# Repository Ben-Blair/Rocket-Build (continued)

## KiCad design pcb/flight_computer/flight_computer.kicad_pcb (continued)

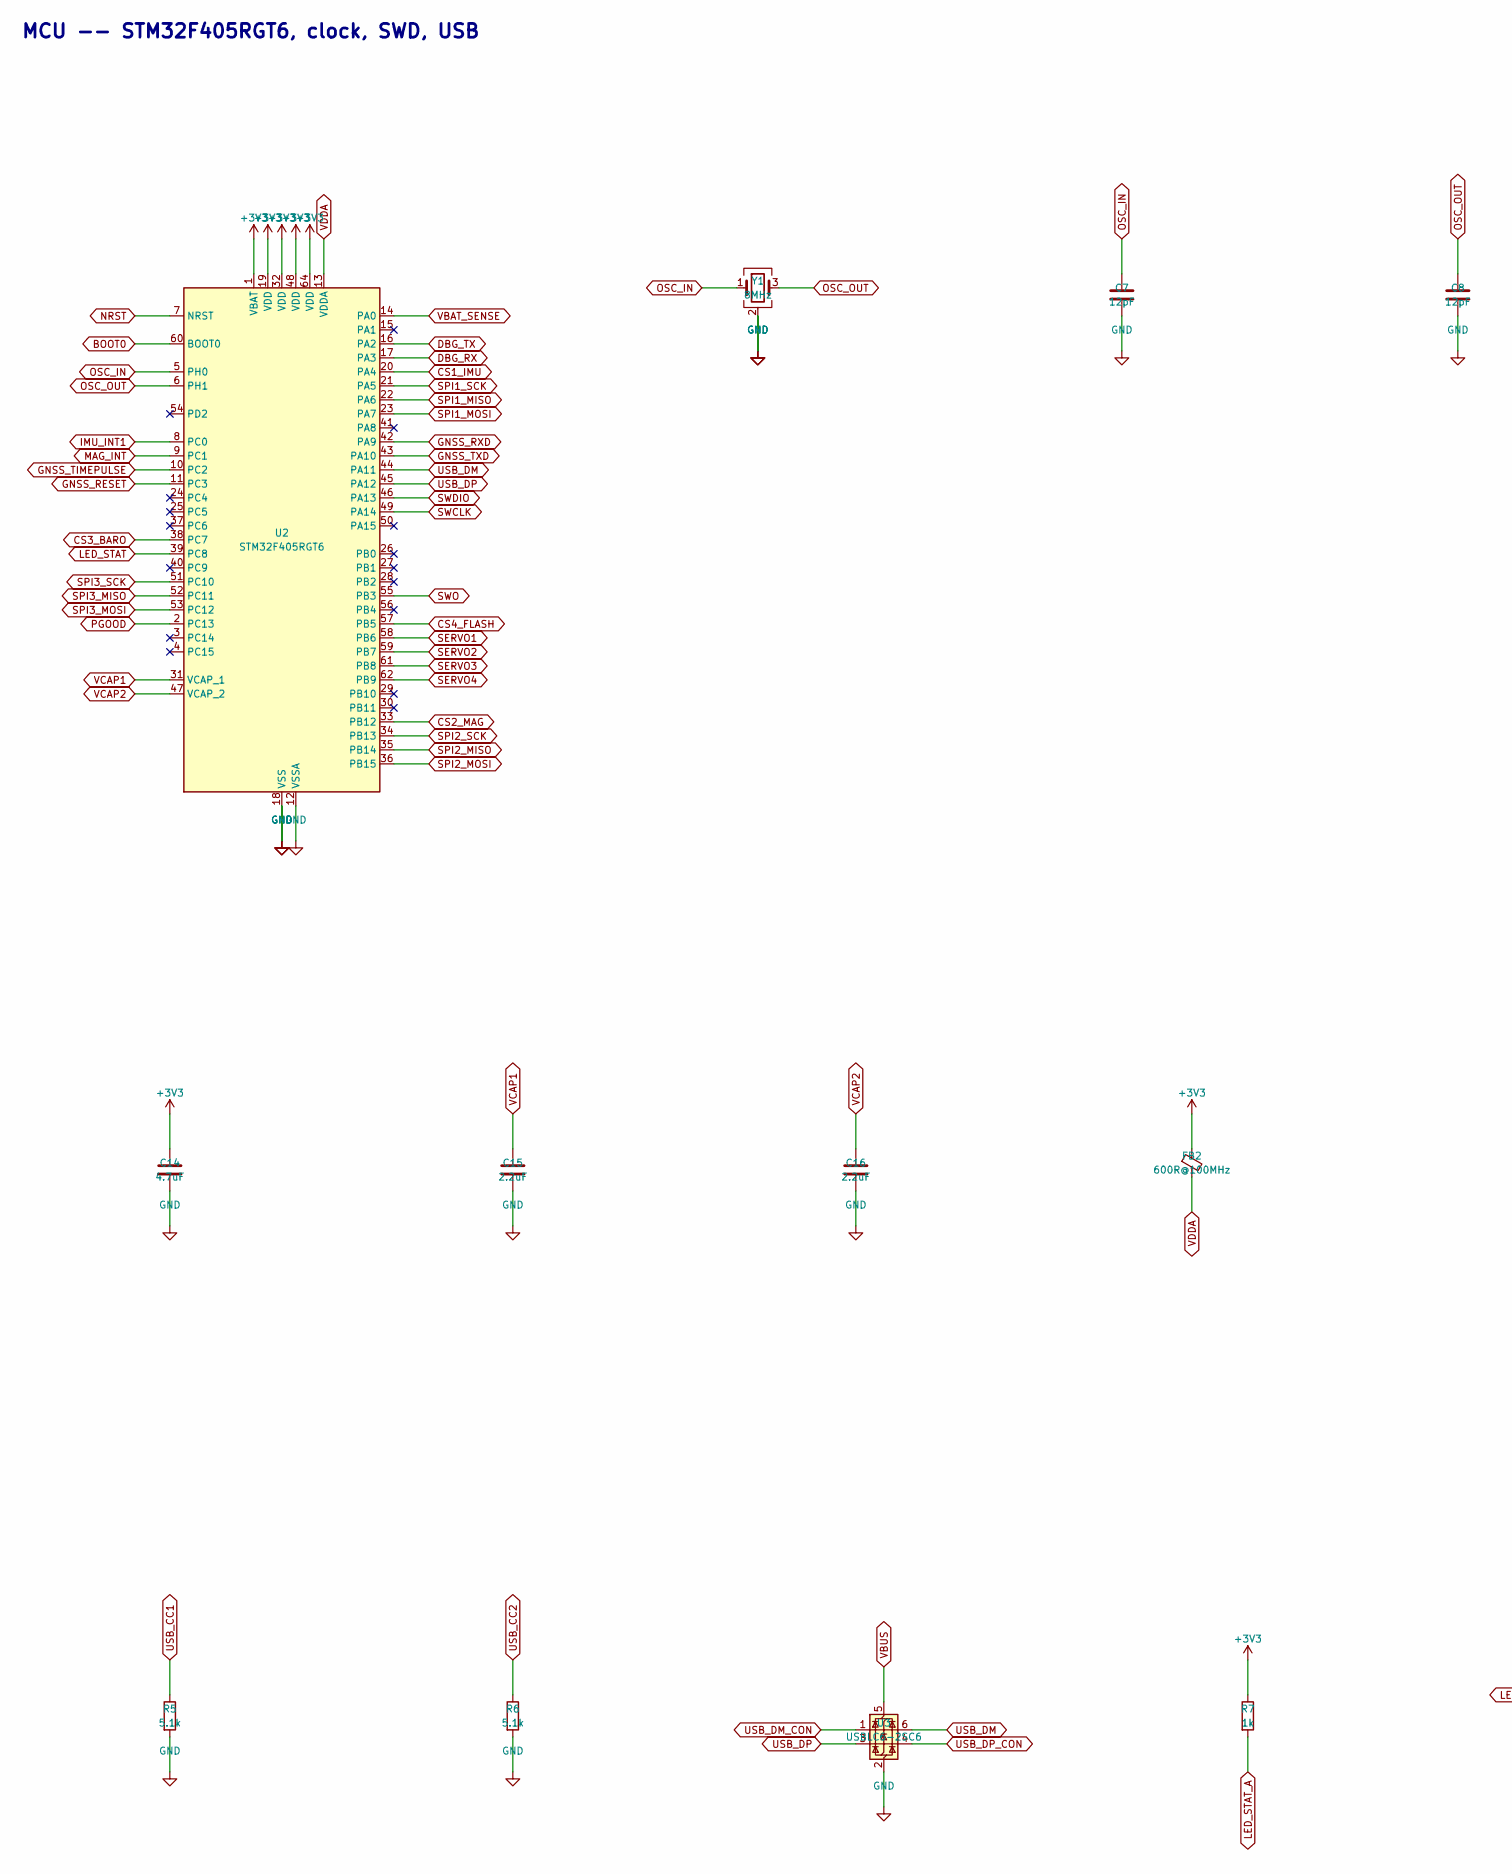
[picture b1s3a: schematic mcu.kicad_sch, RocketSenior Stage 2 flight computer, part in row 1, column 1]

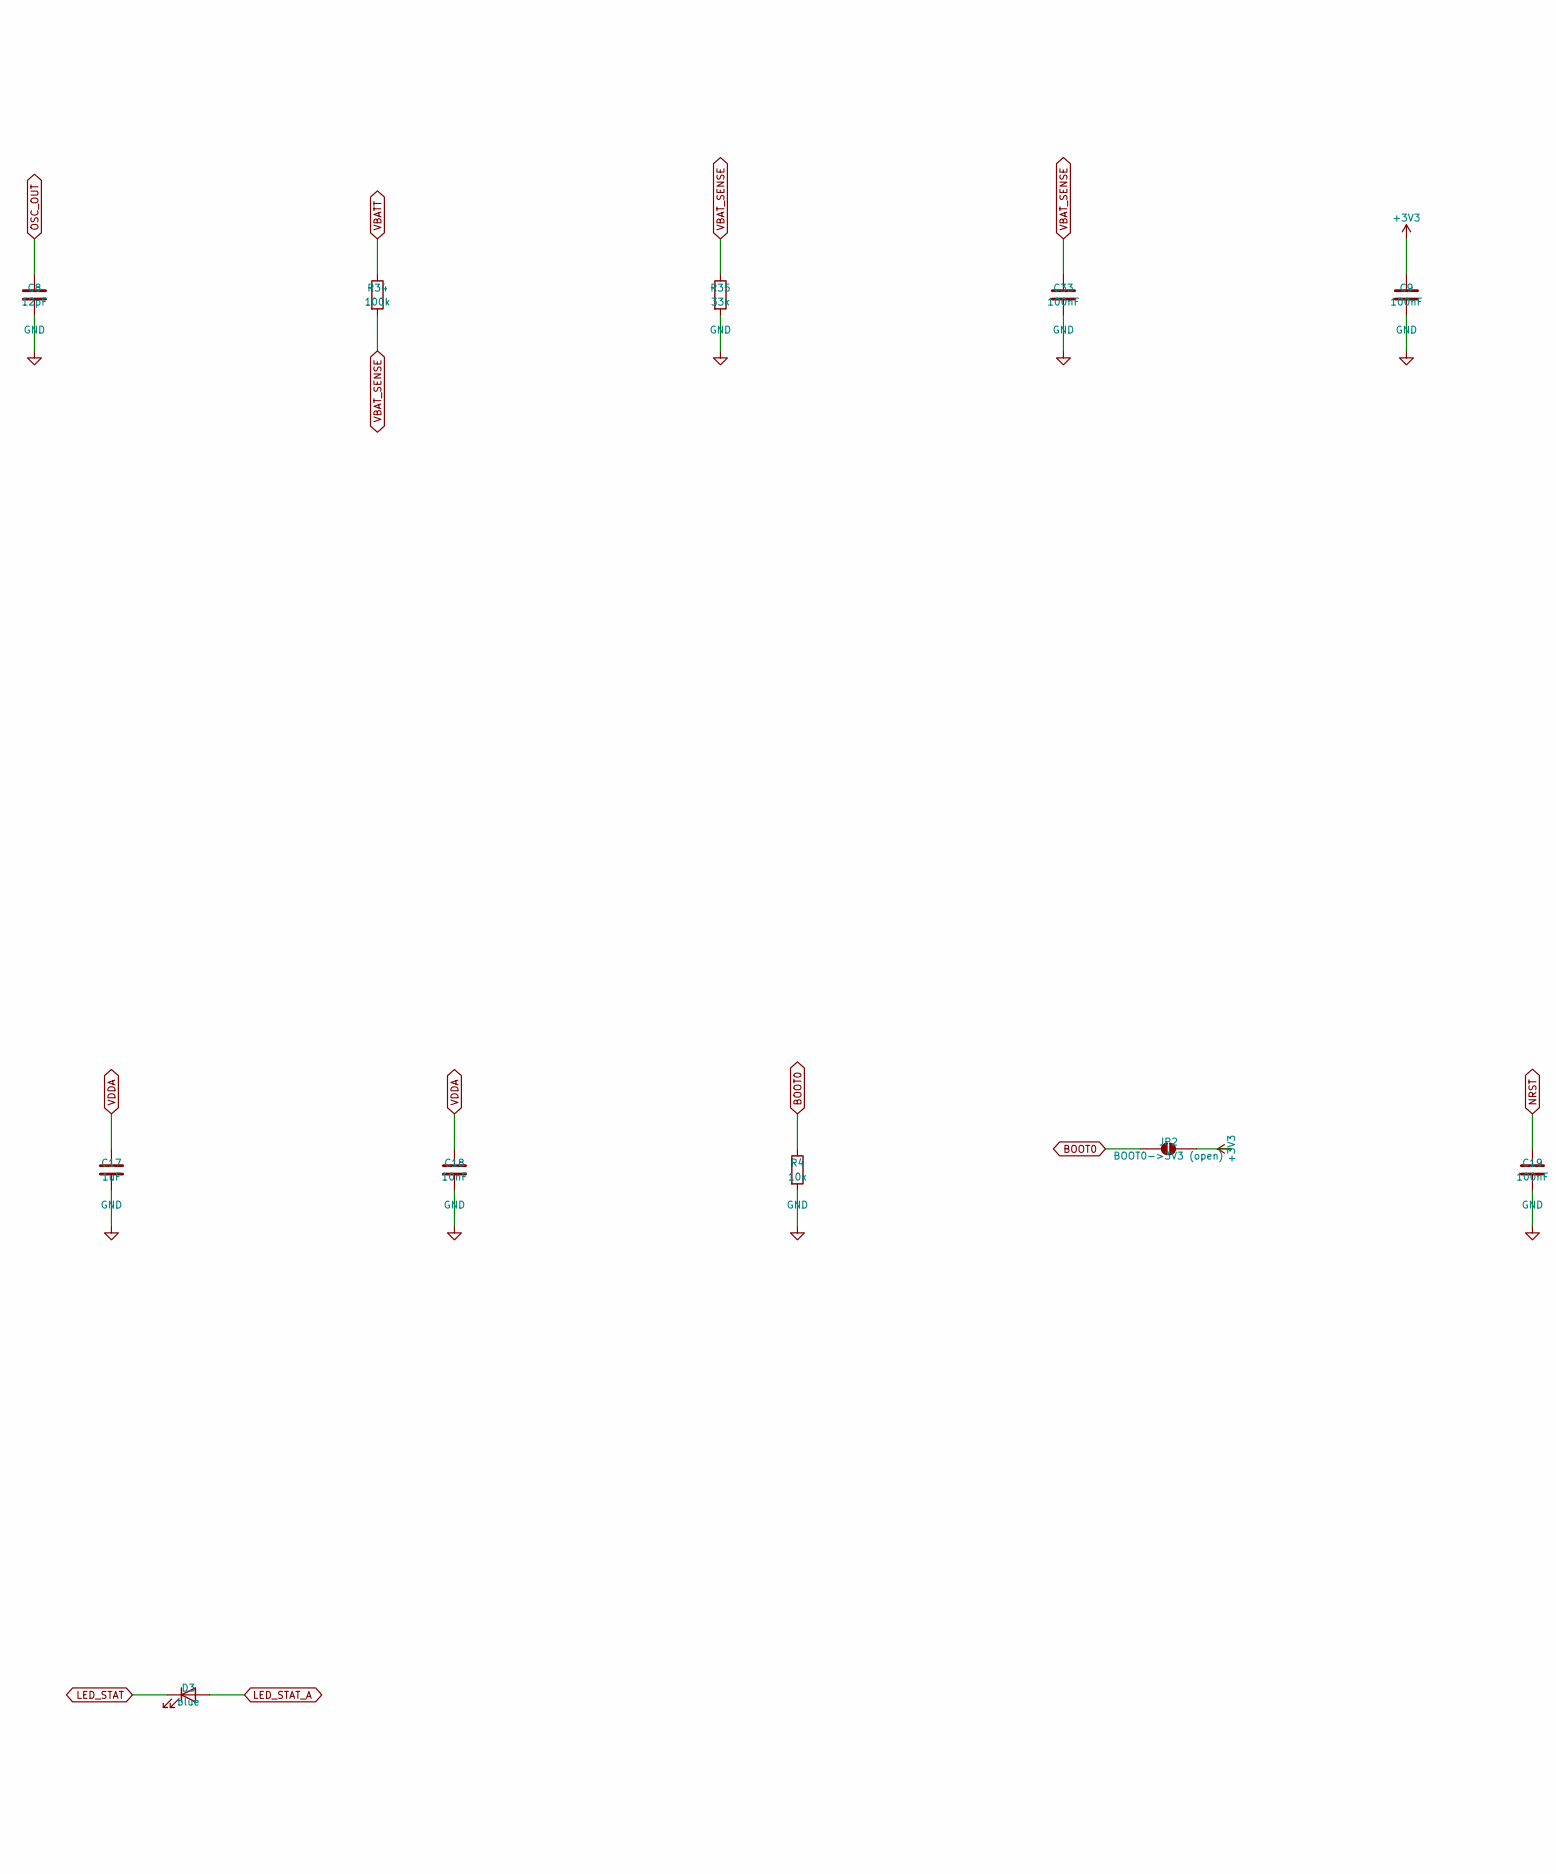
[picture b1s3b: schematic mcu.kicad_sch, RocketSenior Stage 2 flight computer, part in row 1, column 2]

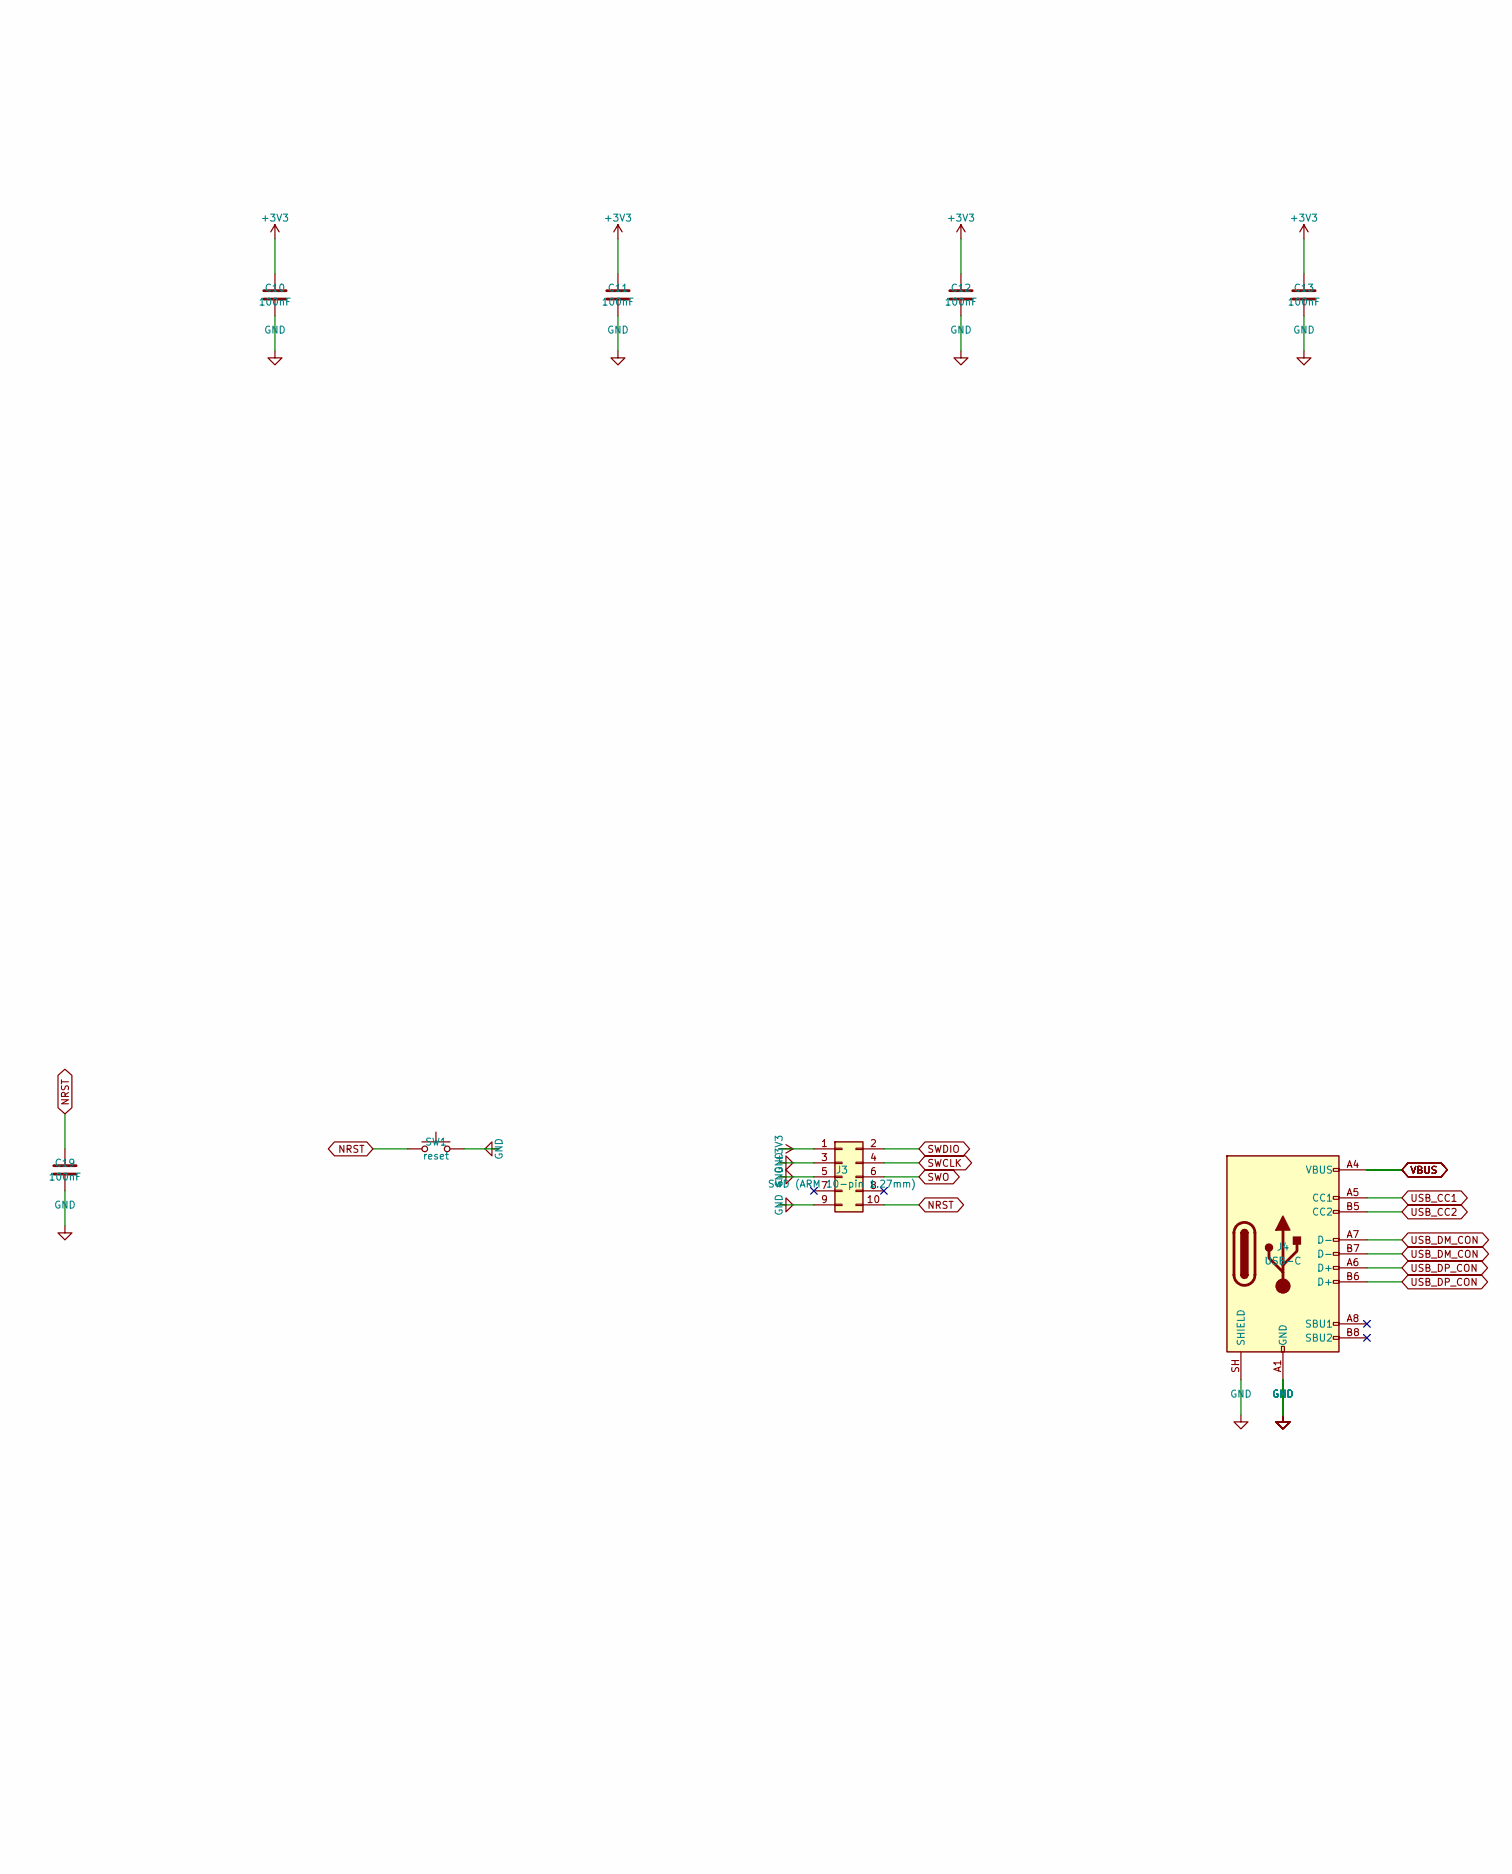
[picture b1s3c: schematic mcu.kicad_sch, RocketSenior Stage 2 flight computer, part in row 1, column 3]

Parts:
C7, C8: 12pF; C_0402_1005Metric
C9, C10, C11, C12, C13, C19, C33: 100nF; C_0402_1005Metric
C14: 4.7uF; C_0805_2012Metric
C15, C16: 2.2uF; C_0805_2012Metric
C17: 1uF; C_0603_1608Metric
C18: 10nF; C_0402_1005Metric
D3: blue; LED_0603_1608Metric
FB2: 600R@100MHz; L_0603_1608Metric
J3: SWD (ARM 10-pin 1.27mm); PinHeader_2x05_P1.27mm_Vertical_SMD
J4: USB-C; USB_C_Receptacle_HRO_TYPE-C-31-M-12
JP2: BOOT0->3V3 (open); SolderJumper-2_P1.3mm_Open_Pad1.0x1.5mm
R4: 10k; R_0402_1005Metric
R5, R6: 5.1k; R_0402_1005Metric
R7: 1k; R_0402_1005Metric
R34: 100k; R_0402_1005Metric
R35: 33k; R_0402_1005Metric
SW1: reset; SW_SPST_TL3342
U2: STM32F405RGT6; LQFP-64_10x10mm_P0.5mm
U3: USBLC6-2SC6; SOT-23-6
Y1: 8MHz; Crystal_SMD_3225-4Pin_3.2x2.5mm

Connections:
+3V3: C9.1, C10.1, C11.1, C12.1, C13.1, C14.1, FB2.1, J3.1, JP2.2 (B), R7.1, U2.1 (VBAT), U2.19 (VDD), U2.32 (VDD), U2.48 (VDD), U2.64 (VDD); also elsewhere on the board
BOOT0: JP2.1 (A), R4.1, U2.60 (BOOT0)
CS1_IMU: U2.20 (PA4); also elsewhere on the board
CS2_MAG: U2.33 (PB12); also elsewhere on the board
CS3_BARO: U2.38 (PC7); also elsewhere on the board
CS4_FLASH: U2.57 (PB5); also elsewhere on the board
DBG_RX: U2.17 (PA3); also elsewhere on the board
DBG_TX: U2.16 (PA2); also elsewhere on the board
GND: C7.2, C8.2, C9.2, C10.2, C11.2, C12.2, C13.2, C14.2, C15.2, C16.2, C17.2, C18.2, C19.2, C33.2, J3.3, J3.5, J3.9, J4.A1 (GND), J4.A12 (GND), J4.B1 (GND), J4.B12 (GND), J4.SH (SHIELD), R4.2, R5.2, R6.2, R35.2, SW1.2, U2.12 (VSSA), U2.18 (VSS), U2.63 (VSS), U3.2 (GND), Y1.2 (G), Y1.4 (G); also elsewhere on the board
GNSS_RESET: U2.11 (PC3); also elsewhere on the board
GNSS_RXD: U2.42 (PA9); also elsewhere on the board
GNSS_TIMEPULSE: U2.10 (PC2); also elsewhere on the board
GNSS_TXD: U2.43 (PA10); also elsewhere on the board
IMU_INT1: U2.8 (PC0); also elsewhere on the board
LED_STAT: D3.1 (K), U2.39 (PC8)
LED_STAT_A: D3.2 (A), R7.2
MAG_INT: U2.9 (PC1); also elsewhere on the board
NRST: C19.1, J3.10, SW1.1, U2.7 (NRST)
OSC_IN: C7.1, U2.5 (PH0), Y1.1
OSC_OUT: C8.1, U2.6 (PH1), Y1.3
PGOOD: U2.2 (PC13); also elsewhere on the board
SERVO1: U2.58 (PB6); also elsewhere on the board
SERVO2: U2.59 (PB7); also elsewhere on the board
SERVO3: U2.61 (PB8); also elsewhere on the board
SERVO4: U2.62 (PB9); also elsewhere on the board
SPI1_MISO: U2.22 (PA6); also elsewhere on the board
SPI1_MOSI: U2.23 (PA7); also elsewhere on the board
SPI1_SCK: U2.21 (PA5); also elsewhere on the board
SPI2_MISO: U2.35 (PB14); also elsewhere on the board
SPI2_MOSI: U2.36 (PB15); also elsewhere on the board
SPI2_SCK: U2.34 (PB13); also elsewhere on the board
SPI3_MISO: U2.52 (PC11); also elsewhere on the board
SPI3_MOSI: U2.53 (PC12); also elsewhere on the board
SPI3_SCK: U2.51 (PC10); also elsewhere on the board
SWCLK: J3.4, U2.49 (PA14)
SWDIO: J3.2, U2.46 (PA13)
SWO: J3.6, U2.55 (PB3)
USB_CC1: J4.A5 (CC1), R5.1
USB_CC2: J4.B5 (CC2), R6.1
USB_DM: U2.44 (PA11), U3.6 (I/O1)
USB_DM_CON: J4.A7 (D-), J4.B7 (D-), U3.1 (I/O1)
USB_DP: U2.45 (PA12), U3.3 (I/O2)
USB_DP_CON: J4.A6 (D+), J4.B6 (D+), U3.4 (I/O2)
VBATT: R34.1; also elsewhere on the board
VBAT_SENSE: C33.1, R34.2, R35.1, U2.14 (PA0)
VBUS: J4.A4 (VBUS), J4.A9 (VBUS), J4.B4 (VBUS), J4.B9 (VBUS), U3.5 (VBUS); also elsewhere on the board
VCAP1: C15.1, U2.31 (VCAP_1)
VCAP2: C16.1, U2.47 (VCAP_2)
VDDA: C17.1, C18.1, FB2.2, U2.13 (VDDA)

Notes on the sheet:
MCU -- STM32F405RGT6, clock, SWD, USB

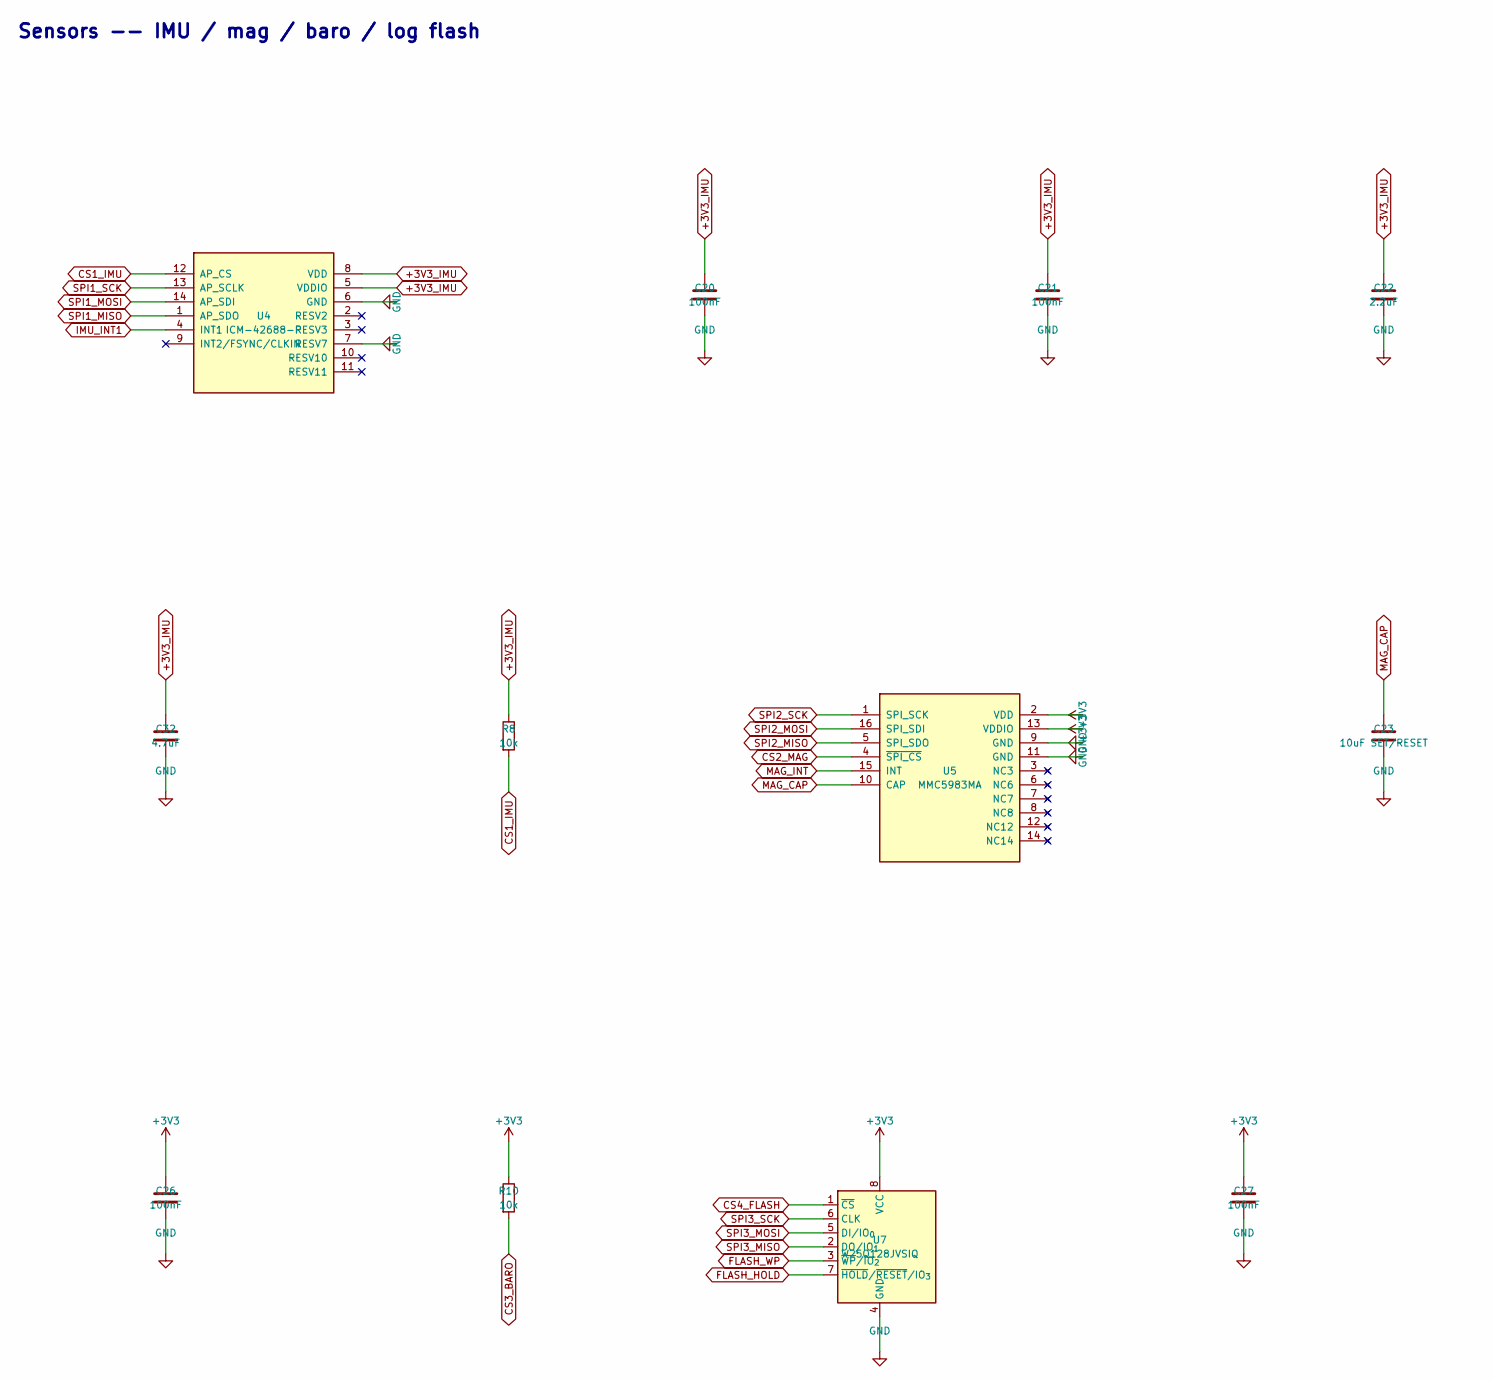
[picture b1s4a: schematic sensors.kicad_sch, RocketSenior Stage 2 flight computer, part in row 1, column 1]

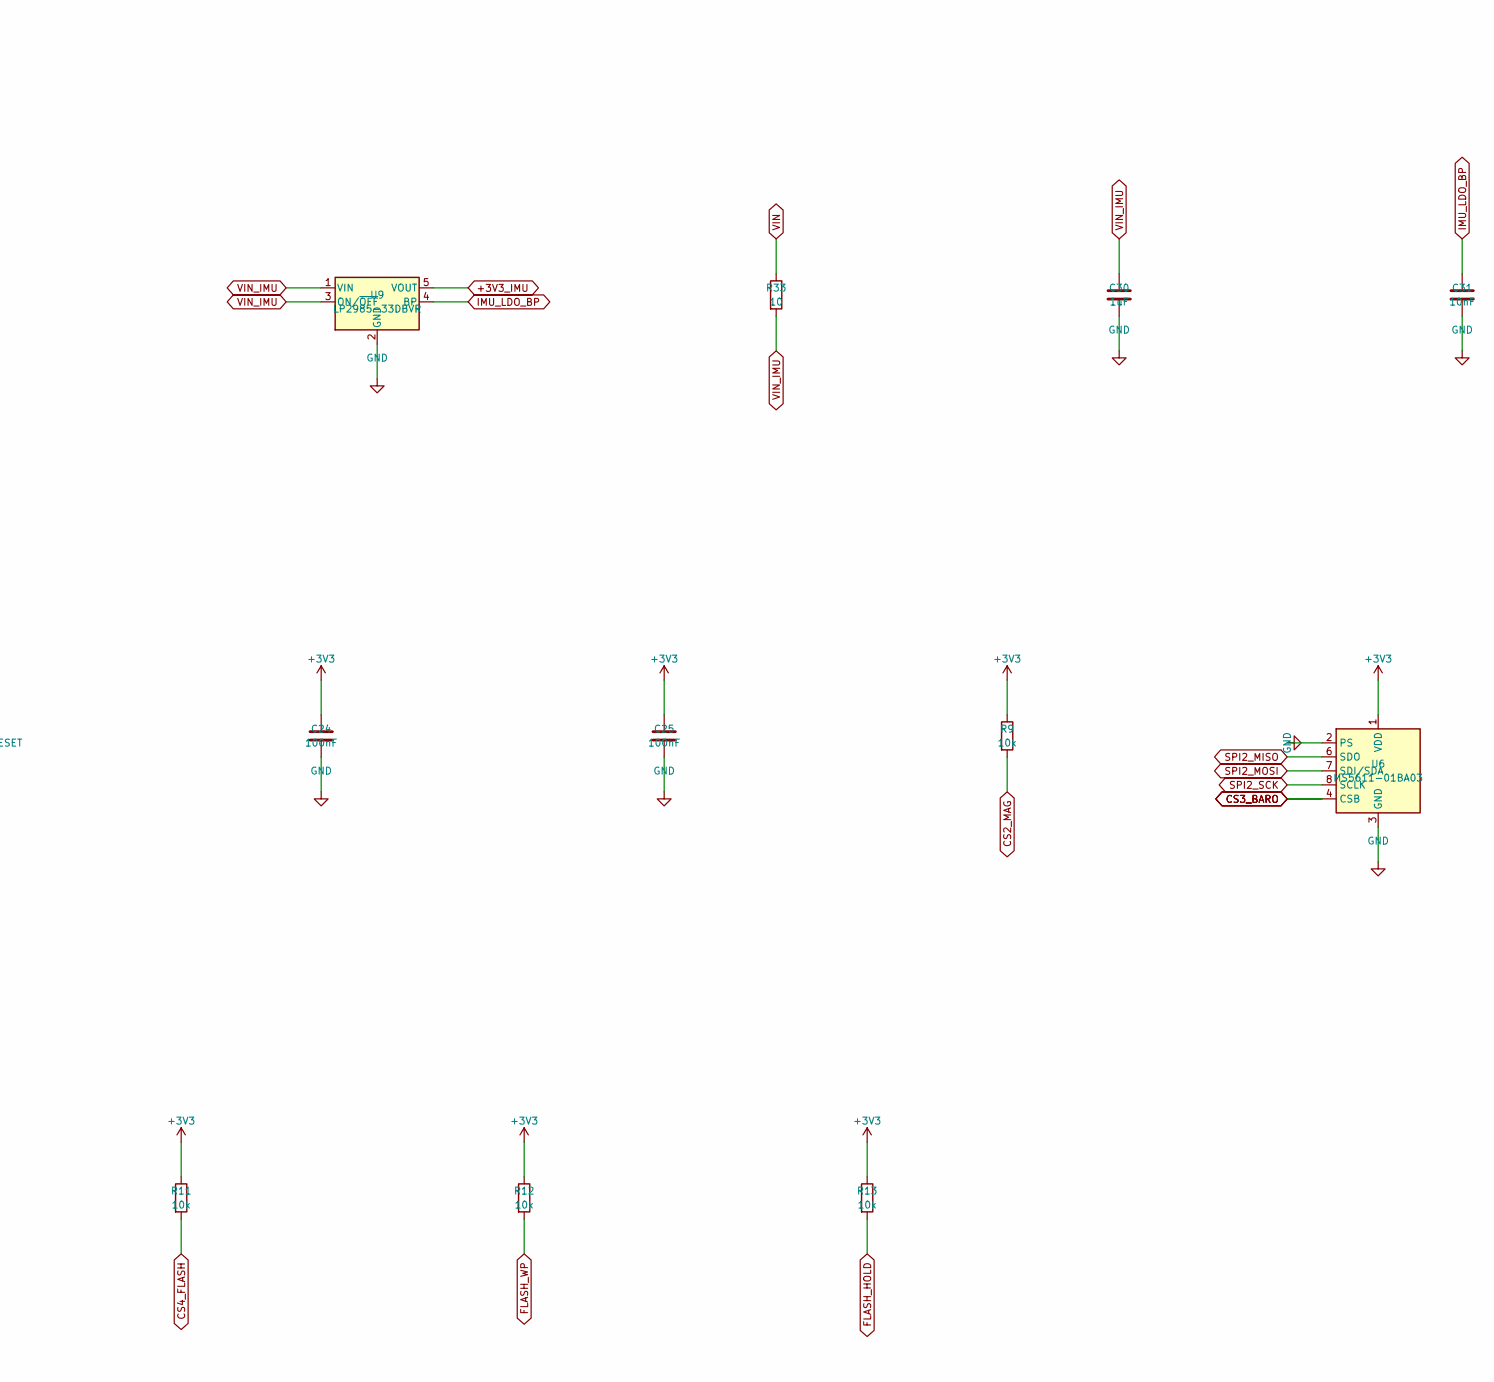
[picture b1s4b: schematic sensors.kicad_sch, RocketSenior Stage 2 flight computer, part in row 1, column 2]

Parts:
C20, C21, C24, C25, C26, C27: 100nF; C_0402_1005Metric
C22: 2.2uF; C_0603_1608Metric
C23: 10uF SET/RESET; C_0805_2012Metric
C30: 1uF; C_0603_1608Metric
C31: 10nF; C_0402_1005Metric
C32: 4.7uF; C_0805_2012Metric
R8, R9, R10, R11, R12, R13: 10k; R_0402_1005Metric
R33: 10; R_0402_1005Metric
U4: ICM-42688-P; LGA-14_3x2.5mm_P0.5mm_LayoutBorder3x4y
U5: MMC5983MA; MMC5983MA_LGA-16_3x3mm_P0.5mm
U6: MS5611-01BA03; LGA-8_3x5mm_P1.25mm
U7: W25Q128JVSIQ; SOIC-8_5.3x5.3mm_P1.27mm
U9: LP2985-33DBVR; SOT-23-5

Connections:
+3V3: C24.1, C25.1, C26.1, C27.1, R9.1, R10.1, R11.1, R12.1, R13.1, U5.2 (VDD), U5.13 (VDDIO), U6.1 (VDD), U7.8 (VCC); also elsewhere on the board
+3V3_IMU: C20.1, C21.1, C22.1, C32.1, R8.1, U4.5 (VDDIO), U4.8 (VDD), U9.5 (VOUT)
CS1_IMU: R8.2, U4.12 (AP_CS); also elsewhere on the board
CS2_MAG: R9.2, U5.4 (~SPI_CS); also elsewhere on the board
CS3_BARO: R10.2, U6.4 (CSB), U6.5 (CSB); also elsewhere on the board
CS4_FLASH: R11.2, U7.1 (~CS); also elsewhere on the board
FLASH_HOLD: R13.2, U7.7 (~HOLD/~RESET/IO_{3})
FLASH_WP: R12.2, U7.3 (~WP/IO_{2})
GND: C20.2, C21.2, C22.2, C23.2, C24.2, C25.2, C26.2, C27.2, C30.2, C31.2, C32.2, U4.6 (GND), U4.7 (RESV7), U5.9 (GND), U5.11 (GND), U6.2 (PS), U6.3 (GND), U7.4 (GND), U9.2 (GND); also elsewhere on the board
IMU_INT1: U4.4 (INT1); also elsewhere on the board
IMU_LDO_BP: C31.1, U9.4 (BP)
MAG_CAP: C23.1, U5.10 (CAP)
MAG_INT: U5.15 (INT); also elsewhere on the board
SPI1_MISO: U4.1 (AP_SDO); also elsewhere on the board
SPI1_MOSI: U4.14 (AP_SDI); also elsewhere on the board
SPI1_SCK: U4.13 (AP_SCLK); also elsewhere on the board
SPI2_MISO: U5.5 (SPI_SDO), U6.6 (SDO); also elsewhere on the board
SPI2_MOSI: U5.16 (SPI_SDI), U6.7 (SDI/SDA); also elsewhere on the board
SPI2_SCK: U5.1 (SPI_SCK), U6.8 (SCLK); also elsewhere on the board
SPI3_MISO: U7.2 (DO/IO_{1}); also elsewhere on the board
SPI3_MOSI: U7.5 (DI/IO_{0}); also elsewhere on the board
SPI3_SCK: U7.6 (CLK); also elsewhere on the board
VIN: R33.1; also elsewhere on the board
VIN_IMU: C30.1, R33.2, U9.1 (VIN), U9.3 (ON/~OFF)

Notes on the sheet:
Sensors -- IMU / mag / baro / log flash

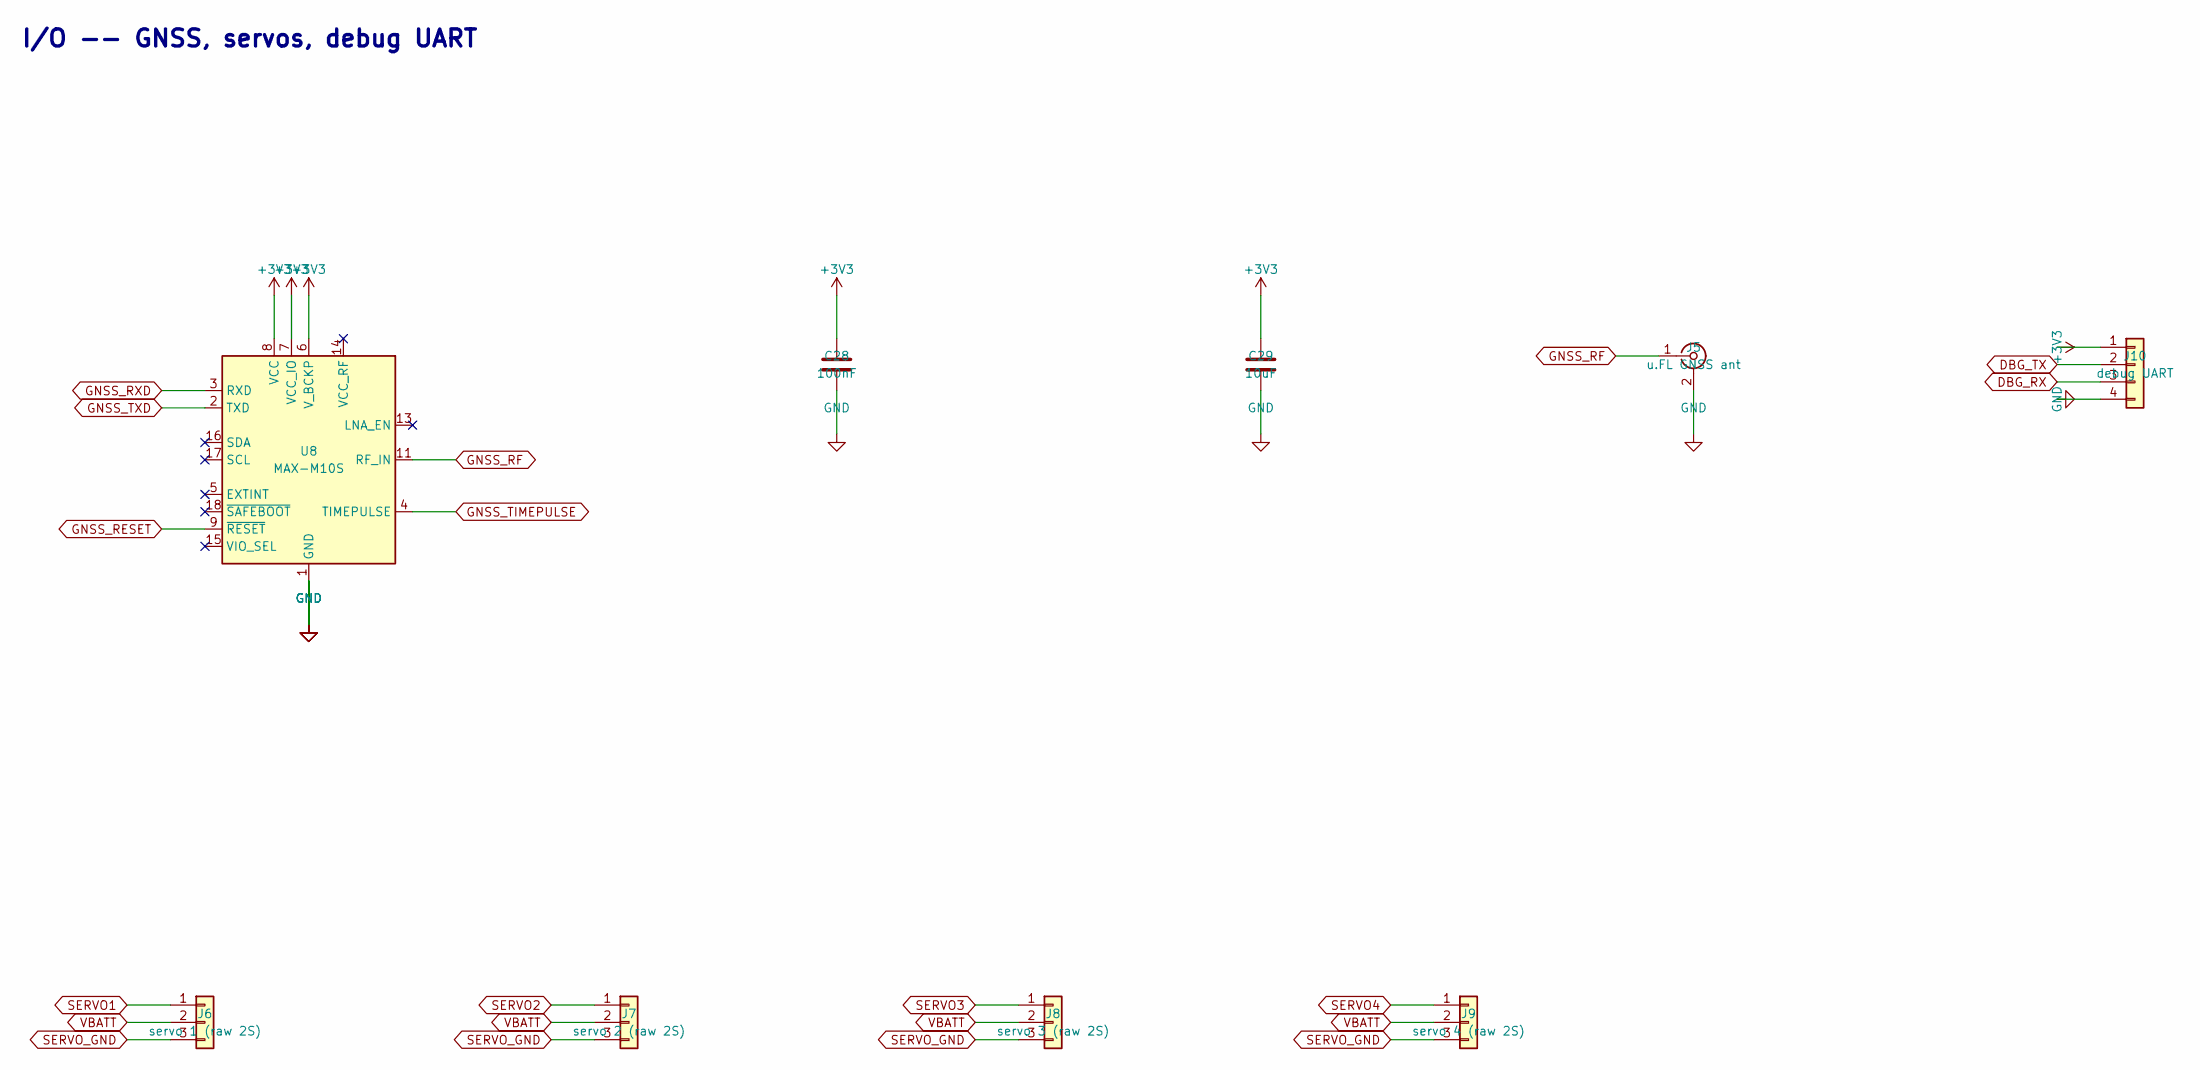
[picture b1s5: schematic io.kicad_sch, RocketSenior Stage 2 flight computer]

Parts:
C28: 100nF; C_0402_1005Metric
C29: 10uF; C_0805_2012Metric
J5: u.FL GNSS ant; U.FL_Hirose_U.FL-R-SMT-1_Vertical
J6: servo 1 (raw 2S); PinHeader_1x03_P2.54mm_Vertical
J7: servo 2 (raw 2S); PinHeader_1x03_P2.54mm_Vertical
J8: servo 3 (raw 2S); PinHeader_1x03_P2.54mm_Vertical
J9: servo 4 (raw 2S); PinHeader_1x03_P2.54mm_Vertical
J10: debug UART; PinHeader_1x04_P2.54mm_Vertical
U8: MAX-M10S; ublox_MAX

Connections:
+3V3: C28.1, C29.1, J10.1, U8.6 (V_BCKP), U8.7 (VCC_IO), U8.8 (VCC); also elsewhere on the board
DBG_RX: J10.3; also elsewhere on the board
DBG_TX: J10.2; also elsewhere on the board
GND: C28.2, C29.2, J5.2 (Ext), J10.4, U8.1 (GND), U8.10 (GND), U8.12 (GND); also elsewhere on the board
GNSS_RESET: U8.9 (~RESET); also elsewhere on the board
GNSS_RF: J5.1 (In), U8.11 (RF_IN)
GNSS_RXD: U8.3 (RXD); also elsewhere on the board
GNSS_TIMEPULSE: U8.4 (TIMEPULSE); also elsewhere on the board
GNSS_TXD: U8.2 (TXD); also elsewhere on the board
SERVO1: J6.1; also elsewhere on the board
SERVO2: J7.1; also elsewhere on the board
SERVO3: J8.1; also elsewhere on the board
SERVO4: J9.1; also elsewhere on the board
SERVO_GND: J6.3, J7.3, J8.3, J9.3; also elsewhere on the board
VBATT: J6.2, J7.2, J8.2, J9.2; also elsewhere on the board

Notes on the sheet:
I/O -- GNSS, servos, debug UART

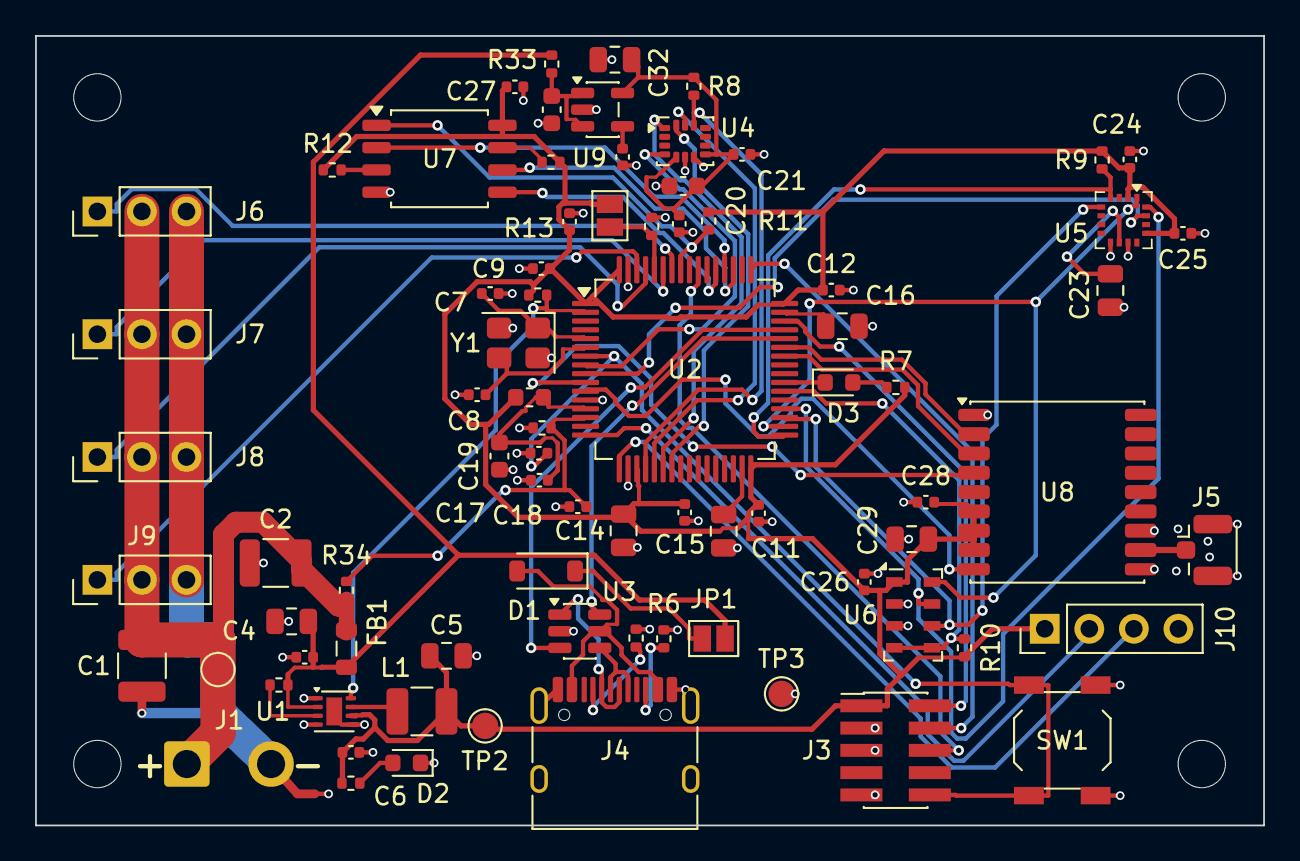
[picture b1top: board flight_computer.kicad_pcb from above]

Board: 4 copper layers, 70.0 x 45.0 mm, 85 parts (0 on the bottom side), 62 nets.

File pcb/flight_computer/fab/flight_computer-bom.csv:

Comment,Designator,Footprint,LCSC Part #
22uF/25V (CL32A226KAJNNNE 25V X5R),"C1,C2",C_1210_3225Metric,C52306
10uF/25V (CL21A106KAYNNNE 25V X5R),C3,C_0805_2012Metric,C15850
100nF/50V (CL05B104KO5NNNC 16V X7R),C4,C_0402_1005Metric,C1525
22uF/16V (CL21A226MAQNNNE 25V X5R),C5,C_0805_2012Metric,C45783
100nF (CL05B104KO5NNNC 16V X7R),"C6,C9,C10,C11,C12,C13,C19,C20,C21,C24,C25,C26,C27,C28,C33",C_0402_1005Metric,C1525
12pF (0402CG120J500NT 50V C0G),"C7,C8",C_0402_1005Metric,C1547
4.7uF (CL21A475KAQNNNE 25V X5R),"C14,C32",C_0805_2012Metric,C1779
2.2uF (CL21B225KAFNNNE 25V X7R),"C15,C16",C_0805_2012Metric,C19110
1uF (CL10A105KA8NNNC 25V X5R),"C17,C30",C_0603_1608Metric,C5673
10nF (CL05B103KB5NNNC 50V X7R),"C18,C31",C_0402_1005Metric,C15195
2.2uF (CL10A225KO8NNNC 16V X5R),C22,C_0603_1608Metric,C23630
10uF SET/RESET (CL21A106KAYNNNE 25V X5R),C23,C_0805_2012Metric,C15850
10uF (CL21A106KAYNNNE 25V X5R),C29,C_0805_2012Metric,C15850
SS14 (B5819W SL 40V 1A SOD-123),D1,D_SOD-123,C8598
green (KT-0603G),D2,LED_0603_1608Metric,C12624
"blue (any 0603 blue, Vf <= 3.0 V)",D3,LED_0603_1608Metric,
600R@100MHz 2A (GZ2012D601TF 600R 0.5A),FB1,L_0805_2012Metric,C1017
600R@100MHz (GZ1608D601TF 600R 0.2A),FB2,L_0603_1608Metric,C1002
SWD (ARM 10-pin 1.27mm) (X1270WVS-2x05B-9TV01),J3,PinHeader_2x05_P1.27mm_Vertical_SMD,C2962219
USB-C (TYPE-C-31-M-12),J4,USB_C_Receptacle_HRO_TYPE-C-31-M-12,C165948
u.FL GNSS ant (U.FL-R-SMT-1(10)),J5,U.FL_Hirose_U.FL-R-SMT-1_Vertical,C88373
2.2uH (LQH32PN2R2NN0L 1.55A),L1,L_1210_3225Metric,C86074
100k (0402WGF1003TCE),"R1,R2,R34",R_0402_1005Metric,C25741
1k (0402WGF1001TCE),"R3,R7",R_0402_1005Metric,C11702
10k (0402WGF1002TCE),"R4,R8,R9,R10,R11,R12,R13",R_0402_1005Metric,C25744
5.1k (0402WGF5101TCE),"R5,R6",R_0402_1005Metric,C25905
10 (0402WGF100JTCE 10R),R33,R_0402_1005Metric,C25077
33k (0402WGF3302TCE),R35,R_0402_1005Metric,C25779
reset (TL3342F160QG),SW1,SW_SPST_TL3342,C2886898
TPS62162DSGT (TPS62162DSGT),U1,Texas_DSG0008A_WSON-8-1EP_2x2mm_P0.5mm_EP0.9x1.6mm,C2863597
STM32F405RGT6 (STM32F405RGT6),U2,LQFP-64_10x10mm_P0.5mm,C15742
USBLC6-2SC6 (USBLC6-2SC6),U3,SOT-23-6,C7519
ICM-42688-P (ICM-42688-P),U4,LGA-14_3x2.5mm_P0.5mm_LayoutBorder3x4y,C1850418
MMC5983MA (MMC5983MA),U5,MMC5983MA_LGA-16_3x3mm_P0.5mm,C404329
MS5611-01BA03 (MS561101BA03-50),U6,LGA-8_3x5mm_P1.25mm,C15639
W25Q128JVSIQ (W25Q128JVSIQ),U7,SOIC-8_5.3x5.3mm_P1.27mm,C97521
MAX-M10S (MAX-M10S-00B),U8,ublox_MAX,C4153167
LP2985-33DBVR (LP2985-33DBVR),U9,SOT-23-5,C95414
8MHz (X32258MOB4SI 8MHz 12pF),Y1,Crystal_SMD_3225-4Pin_3.2x2.5mm,C2682775
